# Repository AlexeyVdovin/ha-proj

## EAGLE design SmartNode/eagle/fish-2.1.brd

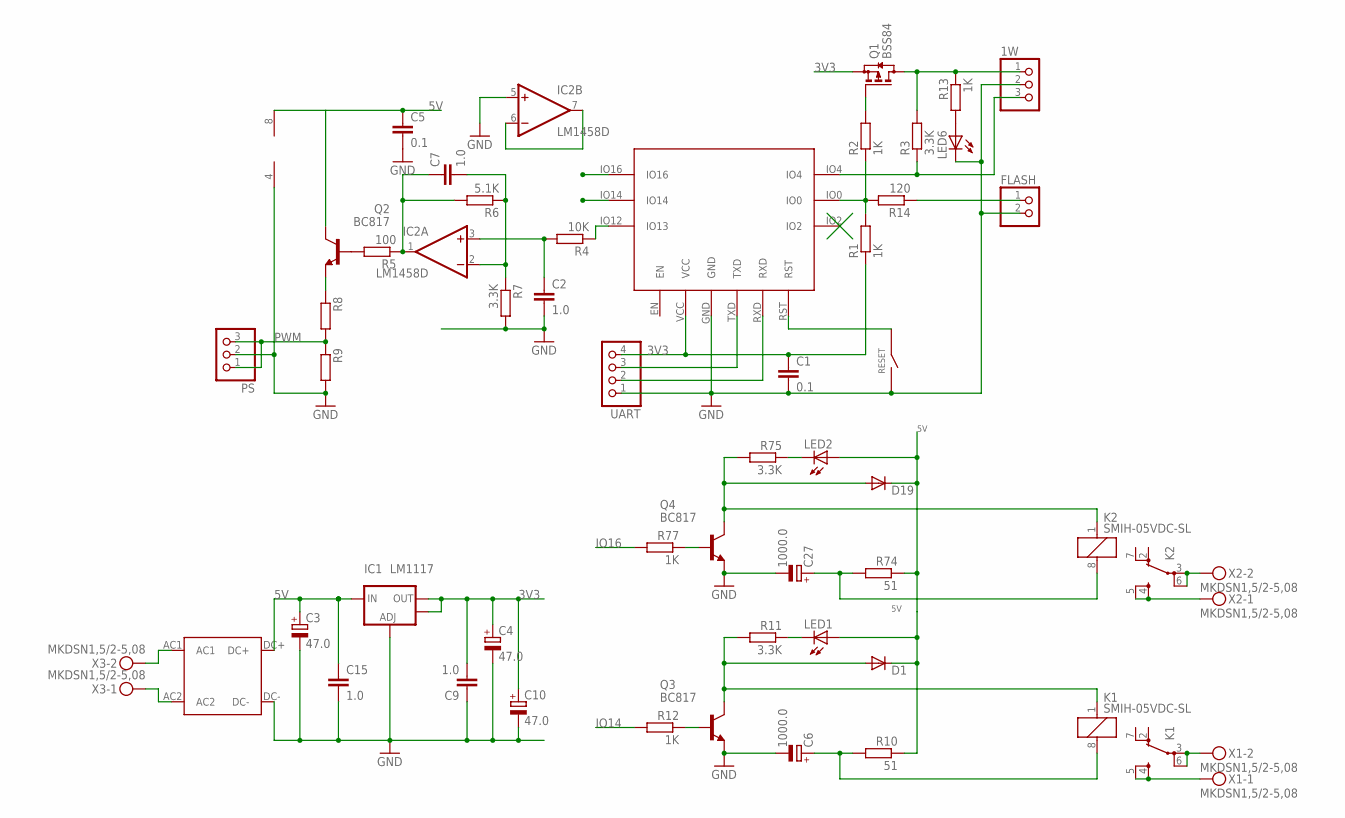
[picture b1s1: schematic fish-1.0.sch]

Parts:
1W: PINHD-1X3/90; 1X03/90
C1, C5: 0.1; C0805
C2, C7, C9, C15: 1.0; C0805
C3, C10: 47.0; SMC_D
C4: 47.0; SMC_B
C6, C27: 1000.0; E3,5-8
D1, D19: DIODE-SOD123; SOD123
ESP-M3: ESP-M3
FLASH: PINHD-1X2/90; 1X02/90
IC1: LM1117; SOT223
IC2: LM1458D; SO08
K1, K2: SMIH-05VDC-SL; FTR-K1C
LED1, LED2, LED6: LEDSMT1206; 1206
PS: PINHD-1X3/90; 1X03/90
Q1: BSS84; SOT23
Q2, Q3, Q4: BC817; SOT23-BEC
R1, R2, R12, R13, R77: 1K; R0603
R3, R7, R11, R75: 3.3K; R0603
R4: 10K; R0603
R5: 100; R0603
R6: 5.1K; R0603
R8, R9: R-EU_R0603; R0603
R10, R74: 51; R1206
R14: 120; R0603
RESET: TACT3X4
U$1: AC-DC/10W-12V; AC-DC/10W
UART: PINHD-1X4/90; 1X04/90
X1, X2, X3: MKDSN1,5/2-5,08

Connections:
1W: 1W.3, ESP-M3.IO4, R3.1
3V3: C1.1, C4.+, C9.2, C10.+, ESP-M3.VCC, IC1.2 (OUT), IC1.4 (OUT), Q1.2 (S), R1.1, UART.4; also elsewhere on the board
5V: C3.+, C5.1, C15.1, D1.C, D19.C, IC1.3 (IN), IC2.8 (V+), LED1.A, LED2.A, Q2.C, R10.1, R74.1, U$1.DC+; also elsewhere on the board
FLASH: FLASH.1, R14.1
GND: 1W.2, C1.2, C2.2, C3.-, C4.-, C5.2, C6.-, C9.1, C10.-, C15.2, C27.-, ESP-M3.GND, FLASH.2, IC1.1 (ADJ), IC2.4 (V-), IC2.5 (+IN), LED6.C, PS.2, Q3.E, Q4.E, R7.2, R9.2, RESET.P$2, U$1.DC-, UART.1; also elsewhere on the board
IO14: ESP-M3.IO14, R12.2
IO16: ESP-M3.IO16, R77.2
unnamed: Q1.1 (G), R2.2
unnamed 10: U$1.AC1, X3.2; also elsewhere on the board
unnamed: ESP-M3.IO12 (IO13), R4.1
unnamed 12: U$1.AC2, X3.1; also elsewhere on the board
unnamed: C2.1, IC2.3 (+IN), R4.2
unnamed 14: C7.1, IC2.1 (OUT), R5.1, R6.2; also elsewhere on the board
unnamed: C7.2, IC2.2 (-IN), R6.1, R7.1
unnamed 16: D1.A, K1.1, Q3.C, R11.2; also elsewhere on the board
unnamed: Q2.B, R5.2
unnamed: Q2.E, R8.1
unnamed: C6.+, K1.8 (2), R10.2
unnamed: LED1.C, R11.1
unnamed 21: Q3.B, R12.1; also elsewhere on the board
unnamed: K1.3 (PA), K1.6 (PB), X1.2
unnamed: ESP-M3.IO0, R1.2, R2.1, R14.2
unnamed: LED6.A, R13.2
unnamed: IC2.6 (-IN), IC2.7 (OUT)
unnamed: K1.4 (SA), K1.5 (SB), X1.1
unnamed 27: D19.A, K2.1, Q4.C, R75.2; also elsewhere on the board
unnamed: C27.+, K2.8 (2), R74.2
unnamed: LED2.C, R75.1
unnamed 30: Q4.B, R77.1; also elsewhere on the board
unnamed: K2.3 (PA), K2.6 (PB), X2.2
unnamed: K2.4 (SA), K2.5 (SB), X2.1
PWM: PS.1, PS.3, R8.2, R9.1; also elsewhere on the board
RST: ESP-M3.RST, RESET.P$1
RX1: ESP-M3.RXD, UART.2
TX1: ESP-M3.TXD, UART.3
VCC: 1W.1, Q1.3 (D), R3.2, R13.1

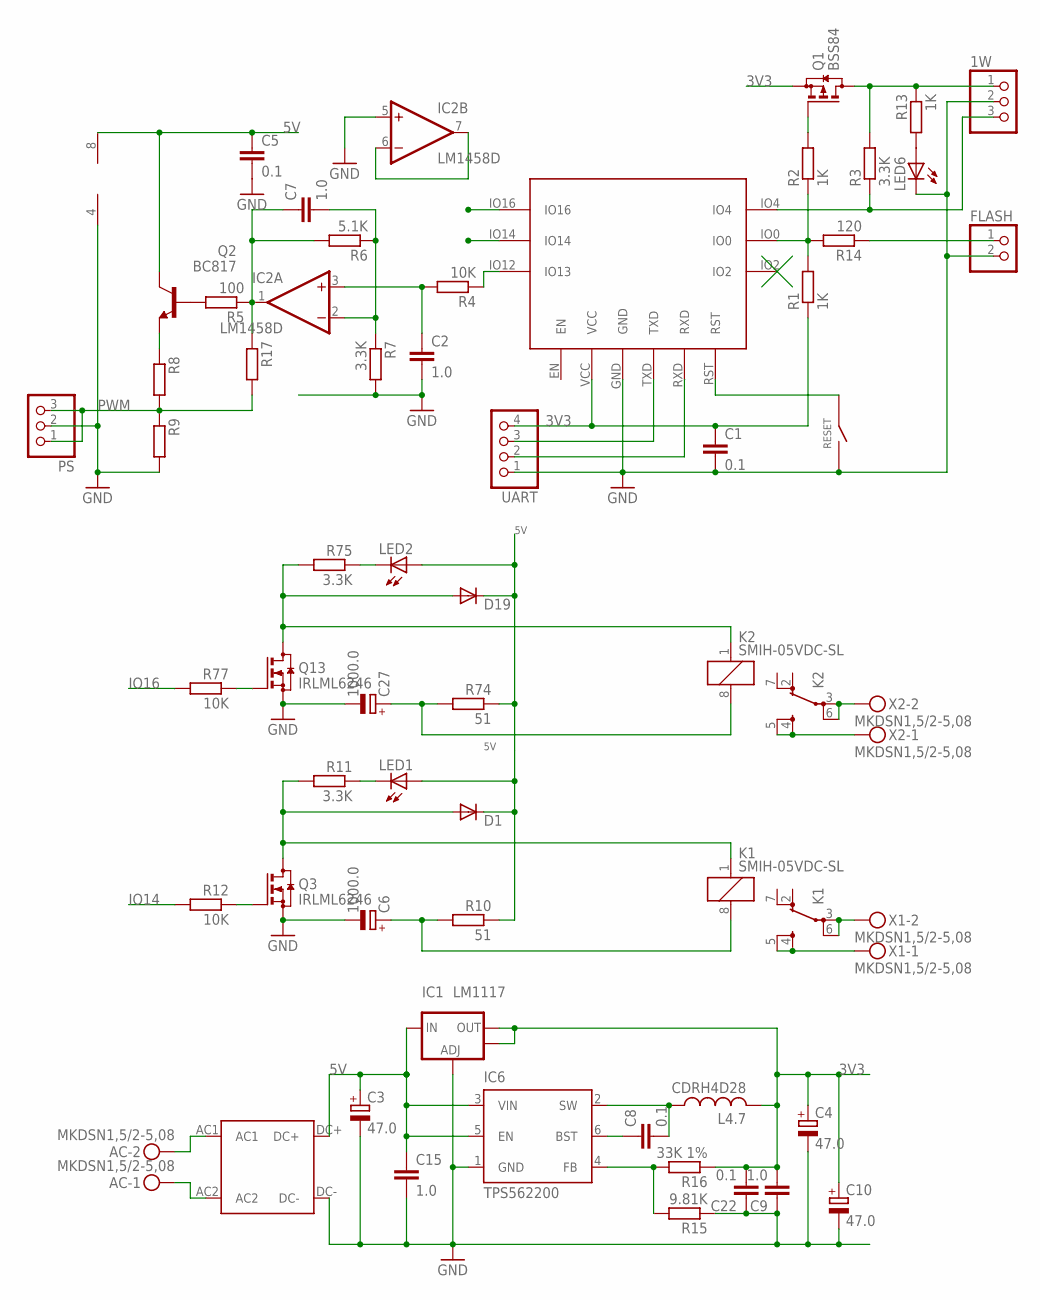
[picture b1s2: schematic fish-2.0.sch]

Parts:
1W: PINHD-1X3/90; 1X03/90
AC: MKDSN1,5/2-5,08
C1, C5, C8, C22: 0.1; C0805
C2, C7, C9, C15: 1.0; C0805
C3, C10: 47.0; SMC_D
C4: 47.0; SMC_B
C6, C27: 1000.0; E3,5-8
D1, D19: DIODE-SOD123; SOD123
ESP-M3: ESP-M3
FLASH: PINHD-1X2/90; 1X02/90
IC1: LM1117; SOT223
IC2: LM1458D; SO08
IC6: TPS562200; TSOT23-6_DDC
K1, K2: SMIH-05VDC-SL; FTR-K1C
L4.7: CDRH4D28
LED1, LED2, LED6: LEDSMT1206; 1206
PS: PINHD-1X3/90; 1X03/90
Q1: BSS84; SOT23
Q2: BC817; SOT23-BEC
Q3, Q13: IRLML6246; SOT23
R1, R2, R13: 1K; R0603
R3, R7, R11, R75: 3.3K; R0603
R4, R12, R77: 10K; R0603
R5: 100; R0603
R6: 5.1K; R0603
R8, R9, R17: R-EU_R0603; R0603
R10, R74: 51; R1206
R14: 120; R0603
R15: 9.81K; R0603
R16: 33K 1%; R0603
RESET: TACT3X4
U$1: AC-DC/10W-12V; AC-DC/10W
UART: PINHD-1X4/90; 1X04/90
X1, X2: MKDSN1,5/2-5,08

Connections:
1W: 1W.3, ESP-M3.IO4, R3.1
3V3: C1.1, C4.+, C9.2, C10.+, C22.2, ESP-M3.VCC, IC1.2 (OUT), IC1.4 (OUT), L4.7.P$2 (2), Q1.2 (S), R1.1, R16.1, UART.4
5V: C3.+, C5.1, C15.1, D1.C, D19.C, IC1.3 (IN), IC2.8 (V+), IC6.3 (VIN), IC6.5 (EN), LED1.A, LED2.A, Q2.C, R10.1, R74.1, U$1.DC+
BOOT: C8.1, IC6.6 (BST)
FB: IC6.4 (FB), R15.2, R16.2
FLASH: FLASH.1, R14.1
GND: 1W.2, C1.2, C2.2, C3.-, C4.-, C5.2, C6.-, C9.1, C10.-, C15.2, C22.1, C27.-, ESP-M3.GND, FLASH.2, IC1.1 (ADJ), IC2.4 (V-), IC2.5 (+IN), IC6.1 (GND), LED6.C, PS.2, Q3.2 (S), Q13.2 (S), R7.2, R9.2, R15.1, RESET.P$2, U$1.DC-, UART.1; also elsewhere on the board
IO14: ESP-M3.IO14, R12.2
IO16: ESP-M3.IO16, R77.2
unnamed: Q1.1 (G), R2.2
unnamed 10: AC.2, U$1.AC1; also elsewhere on the board
unnamed: ESP-M3.IO12 (IO13), R4.1
unnamed 12: AC.1, U$1.AC2; also elsewhere on the board
unnamed: C2.1, IC2.3 (+IN), R4.2
unnamed: C7.1, IC2.1 (OUT), R5.1, R6.2, R17.1
unnamed: C7.2, IC2.2 (-IN), R6.1, R7.1
unnamed 16: D1.A, K1.1, Q3.3 (D), R11.2; also elsewhere on the board
unnamed: Q2.B, R5.2
unnamed: Q2.E, R8.1
unnamed: C6.+, K1.8 (2), R10.2
unnamed: LED1.C, R11.1
unnamed 21: Q3.1 (G), R12.1; also elsewhere on the board
unnamed: K1.3 (PA), K1.6 (PB), X1.2
unnamed: ESP-M3.IO0, R1.2, R2.1, R14.2
unnamed: LED6.A, R13.2
unnamed: IC2.6 (-IN), IC2.7 (OUT)
unnamed: K1.4 (SA), K1.5 (SB), X1.1
unnamed 27: D19.A, K2.1, Q13.3 (D), R75.2; also elsewhere on the board
unnamed: C27.+, K2.8 (2), R74.2
unnamed: LED2.C, R75.1
unnamed 30: Q13.1 (G), R77.1; also elsewhere on the board
unnamed: K2.3 (PA), K2.6 (PB), X2.2
unnamed: K2.4 (SA), K2.5 (SB), X2.1
PWM: PS.1, PS.3, R8.2, R9.1, R17.2
RST: ESP-M3.RST, RESET.P$1
RX1: ESP-M3.RXD, UART.2
SW: C8.2, IC6.2 (SW), L4.7.P$1 (1)
TX1: ESP-M3.TXD, UART.3
VCC: 1W.1, Q1.3 (D), R3.2, R13.1

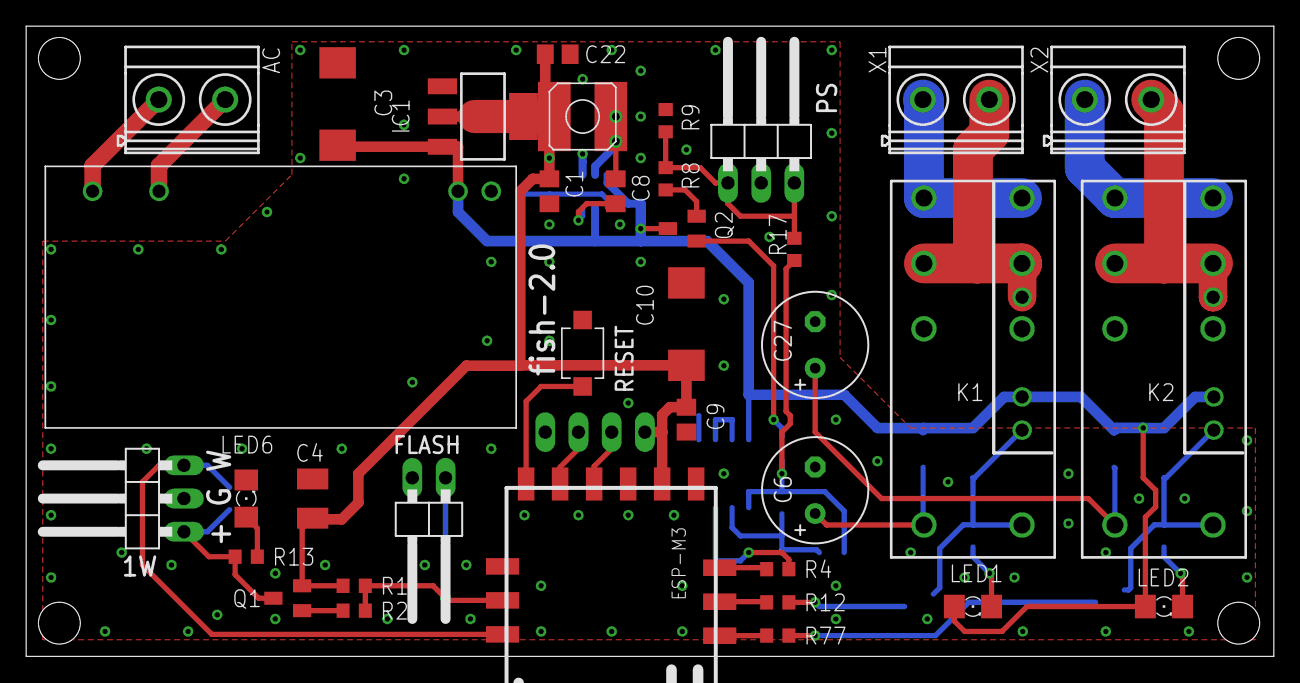
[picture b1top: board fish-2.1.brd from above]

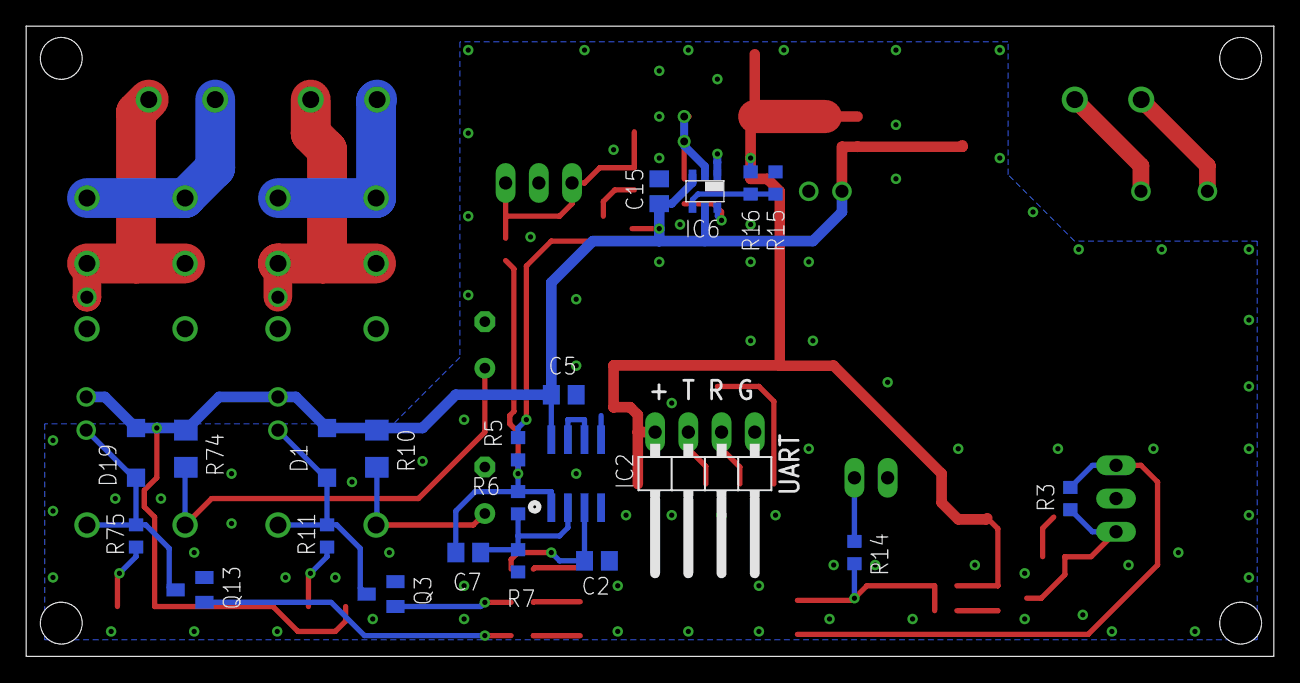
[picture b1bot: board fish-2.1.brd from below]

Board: 2 copper layers, 95.4 x 48.2 mm, 58 parts (22 on the bottom side), 39 nets.

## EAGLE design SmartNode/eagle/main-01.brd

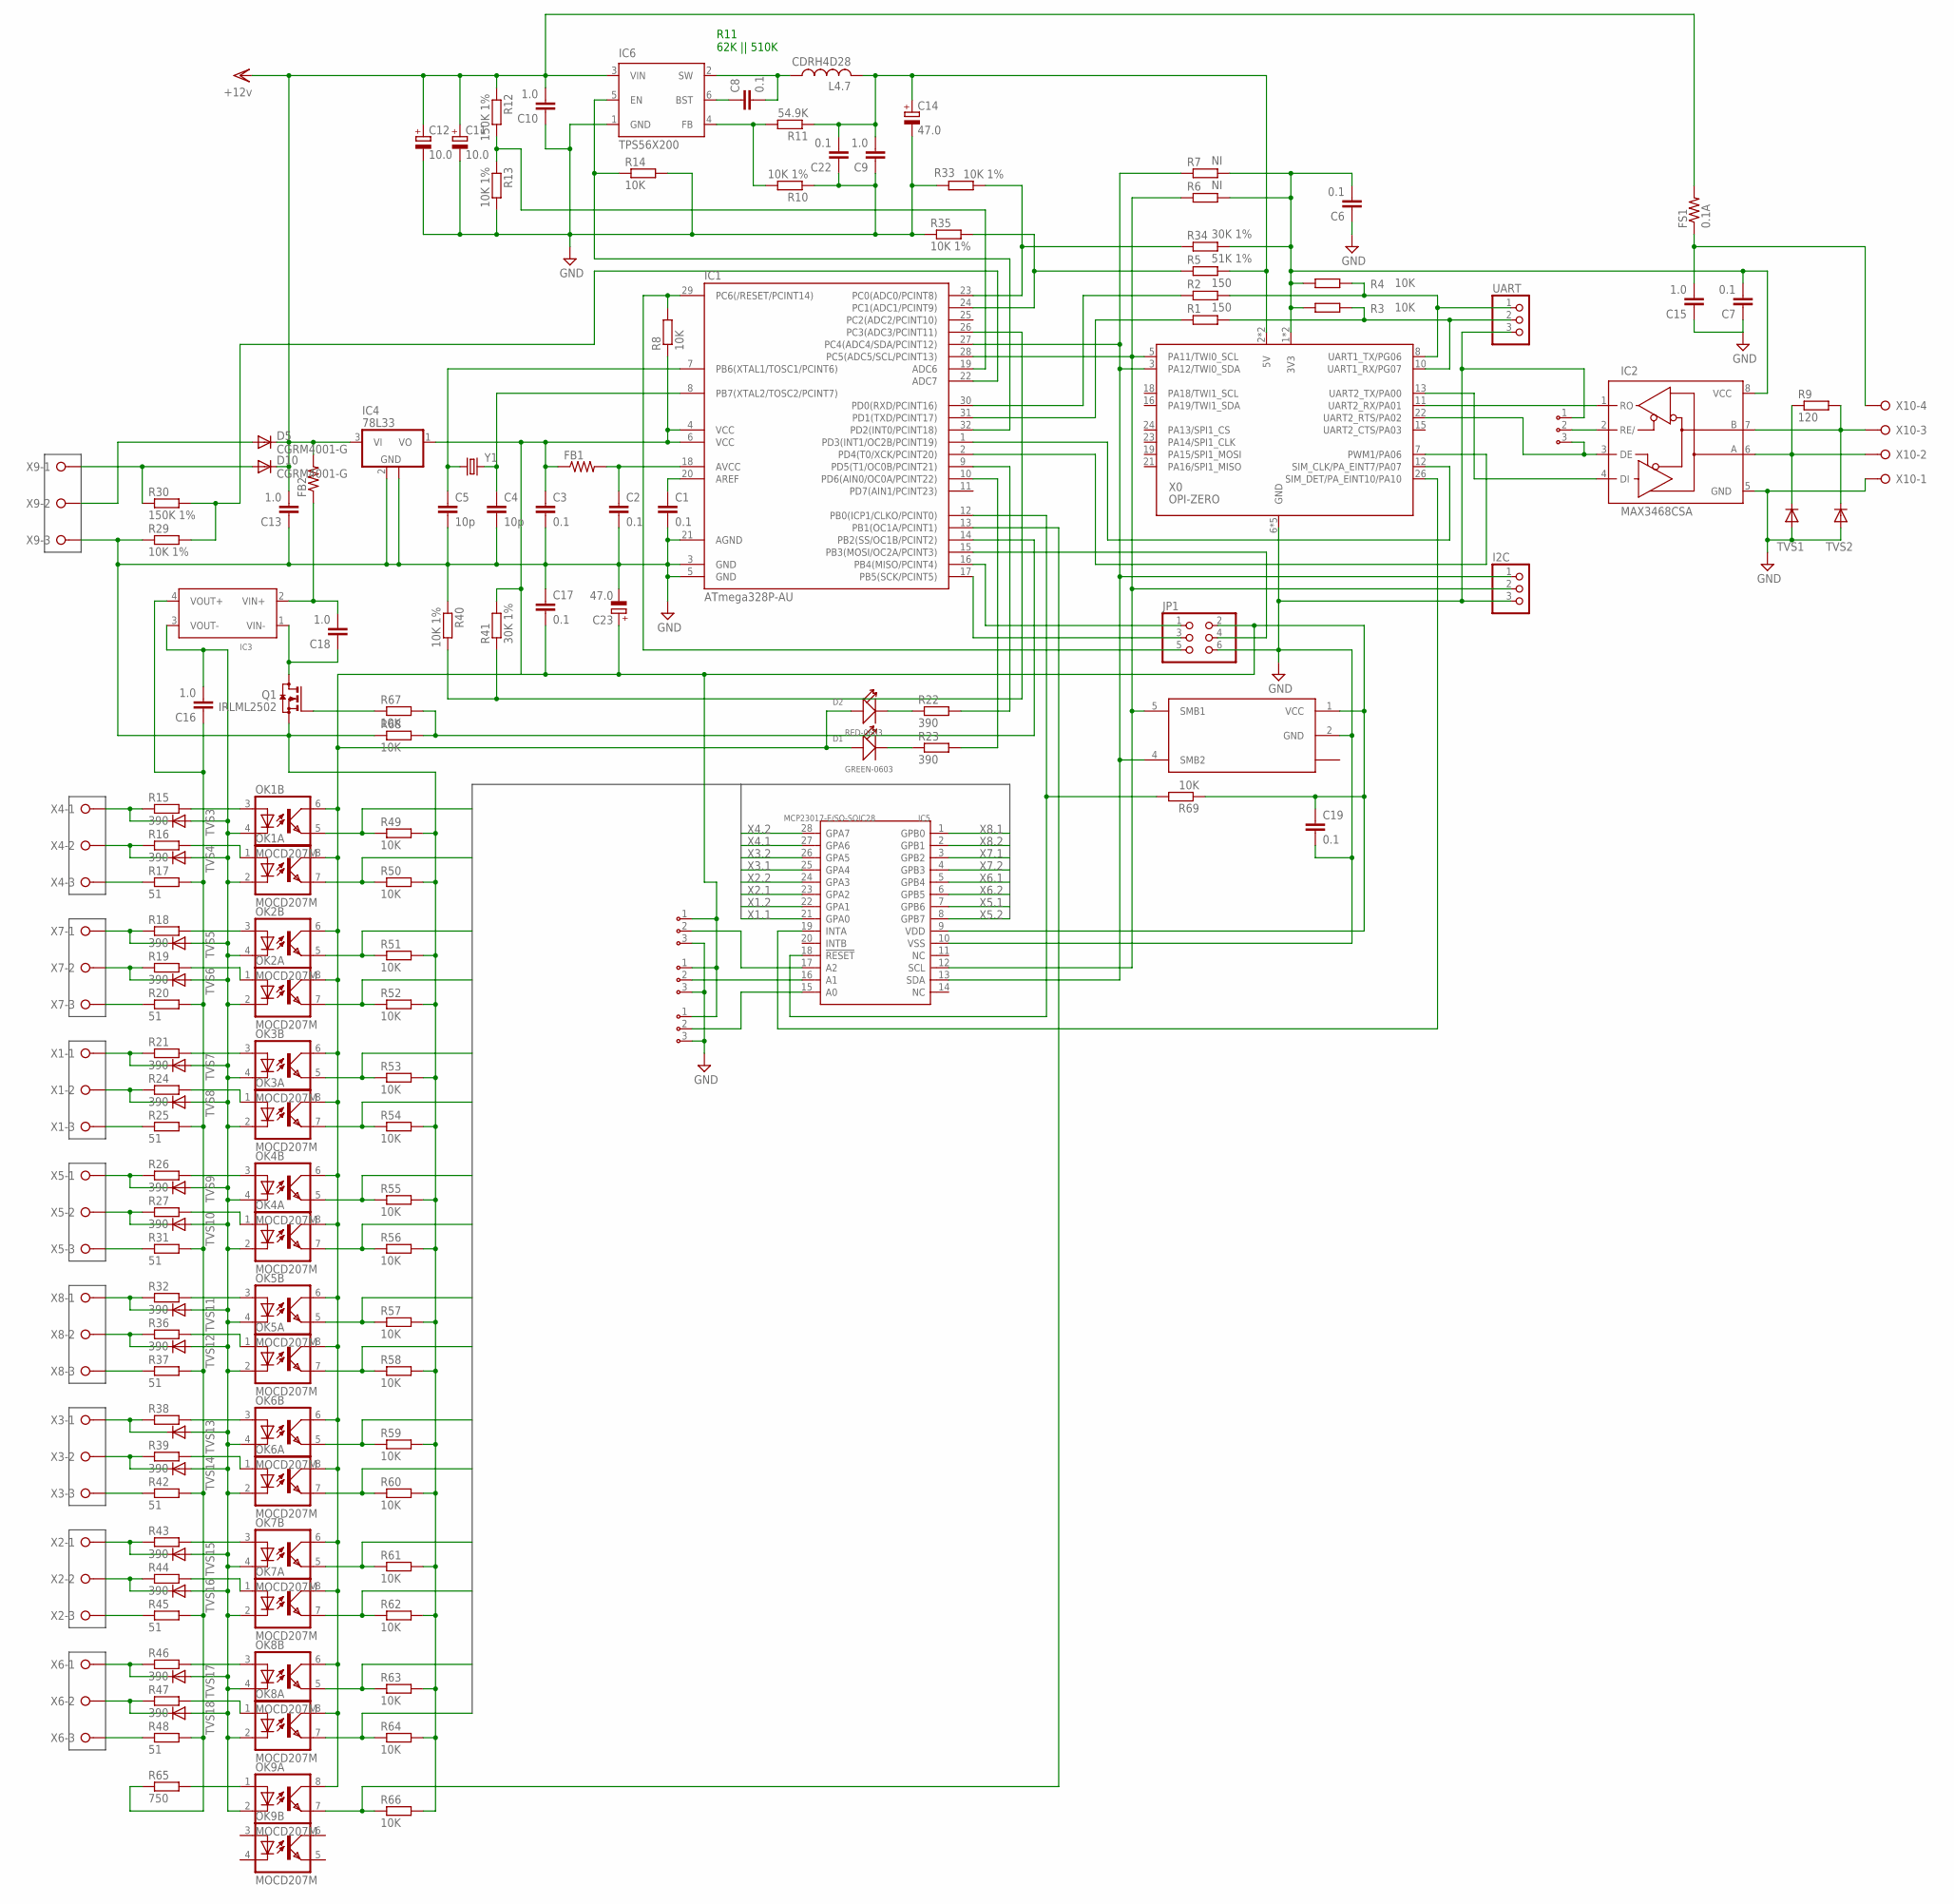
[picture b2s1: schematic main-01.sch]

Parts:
4: ADDR3PIN0603; 0603-3PIN
A0, A1, A2: ADDR3PIN0603; 0603-3PIN
C1, C2, C3, C17, C19: 0.1; C0603
C4, C5: 10p; C0603
C6, C7, C8, C22: 0.1; C0805
C9: 1.0; C0805
C10, C13, C15, C16, C18: 1.0; C1206
C11, C12: 10.0; C/6032-28R
C14, C23: 47.0; B/3528-21R
D1: GREEN-0603; LED-0603
D2: RED-0603; LED-0603
D5, D10: CGRM4001-G; SOD-123_MINI-SMA
FB1: R-US_R0805; R0805
FB2: R-US_R1206; R1206
FS1: 0.1A; R1210
I2C: PINHD-1X3; 1X03
IC1: ATmega328P-AU; TQFP32-08
IC2: MAX3468CSA; SO08
IC3: DC-DC-CONV-4PIN-ISOLATINGMURATA-NME-05-12-SERIES; DC-DC-MURATA-NME-05-12-SERIES
IC4: 78L33; SOT89
IC5: MCP23017-E/SO-SOIC28; SOIC28-1.27-17.9X7.5MM
IC6: TPS56X200; TSOT23-6_DDC
IC7: LTC1694; SOT23-5
JP1: PINHD-2X3; 2X03
L4.7: CDRH4D28
OK1, OK2, OK3, OK4, OK5, OK6, OK7, OK8, OK9: MOCD207M; SOIC08-FAIRCHILD
Q1: IRLML2502; SOT23
R1, R2: 150; R0603
R3, R4, R8, R14, R49, R50, R51, R52, R53, R54, R55, R56, R57, R58, R59, R60, R61, R62, R63, R64, R66, R67, R68, R69: 10K; R0603
R5: 51K 1%; R0603
R6, R7: NI; R0603
R9: 120; R1206
R10, R13, R29, R33, R35, R40: 10K 1%; R0603
R11: 54.9K; R0603
R12, R30: 150K 1%; R0603
R15, R16, R18, R19, R21, R22, R23, R24, R26, R27, R32, R36, R39, R43, R44, R46, R47: 390; R0603
R17, R20, R25, R31, R37, R42, R45, R48: 51; R0603
R34, R41: 30K 1%; R0603
R38: R-EU_R0603; R0603
R65: 750; R0603
TVS1, TVS2, TVS3, TVS4, TVS5, TVS6, TVS7, TVS8, TVS9, TVS10, TVS11, TVS12, TVS13, TVS14, TVS15, TVS16, TVS17, TVS18: DIODE-SOD323-W; SOD323-W
UART: PINHD-1X3; 1X03
X0: OPI-ZERO; OPI0
X1, X2, X3, X4, X5, X6, X7, X8, X9: W237-03P; W237-133
X10: W237-04P; W237-4P
Y1: CRYSTALHC49US; HC49US

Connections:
12V: C10.2, C11.+, C12.+, C13.2, D5.C, D10.C, FB2.2, FS1.2, IC4.3 (VI), IC6.3 (VIN), R12.1
GND: 4.1, A0.3, A1.3, A2.3, C1.2, C2.2, C3.2, C4.2, C5.2, C6.1, C7.1, C9.1, C10.1, C11.-, C12.-, C13.1, C14.-, C15.1, C17.1, C19.2, C22.1, C23.-, I2C.3, IC1.3 (GND), IC1.5 (GND), IC1.21 (AGND), IC2.5 (GND), IC4.2 (GND), IC4.2@1 (GND), IC5.10 (VSS), IC6.1 (GND), IC7.2 (GND), JP1.6, Q1.2 (S), R10.1, R13.2, R14.2, R29.1, R33.2, R35.1, R40.1, R49.2, R50.2, R51.2, R52.2, R53.2, R54.2, R55.2, R56.2, R57.2, R58.2, R59.2, R60.2, R61.2, R62.2, R63.2, R64.2, R66.2, R68.1, TVS1.A, TVS2.A, UART.3, X0.6 (GND), X0.9 (GND), X0.14 (GND), X0.20 (GND), X0.25 (GND), X9.3, X10.1
unnamed: 4.3, IC2.3 (DE), X0.22 (UART2_RTS/PA02)
unnamed: IC2.1 (RO), X0.11 (UART2_RX/PA01)
unnamed: C8.2, IC6.2 (SW), L4.7.P$1 (1)
unnamed: C4.1, IC1.8 (PB7(XTAL2/TOSC2/PCINT7)), Y1.2
unnamed: IC1.30 (PD0(RXD/PCINT16)), R2.1
unnamed: IC1.31 (PD1(TXD/PCINT17)), R1.1
unnamed: R1.2, R3.2, UART.2, X0.10 (UART1_RX/PG07)
unnamed: R2.2, R4.2, UART.1, X0.8 (UART1_TX/PG06)
unnamed: IC2.4 (DI), X0.13 (UART2_TX/PA00)
unnamed: C5.1, IC1.7 (PB6(XTAL1/TOSC1/PCINT6)), Y1.1
unnamed: IC1.24 (PC1(ADC1/PCINT9)), R5.1, R35.2
unnamed: D5.A, X9.2
unnamed: IC1.29 (PC6(/RESET/PCINT14)), JP1.5, R8.2
unnamed: OK1.3 (A), R15.2
unnamed: C1.1, IC1.20 (AREF)
unnamed: C2.1, FB1.2, IC1.18 (AVCC)
unnamed: C8.1, IC6.6 (BST)
unnamed: IC1.15 (PB3(MOSI/OC2A/PCINT3)), JP1.4
unnamed: IC1.17 (PB5(SCK/PCINT5)), JP1.3
unnamed: IC1.16 (PB4(MISO/PCINT4)), JP1.1
unnamed: IC2.6 (A), R9.1, TVS1.C, X10.2
unnamed: IC6.4 (FB), R10.2, R11.2
unnamed: IC2.7 (B), R9.2, TVS2.C, X10.3
unnamed: C15.2, FS1.1, X10.4
unnamed: IC1.19 (ADC6), R12.2, R13.1
unnamed: R15.1, TVS3.C, X4.1
unnamed: IC1.32 (PD2(INT0/PCINT18)), IC6.5 (EN), R14.1
unnamed: R16.1, TVS4.C, X4.2
unnamed: IC1.1 (PD3(INT1/OC2B/PCINT19)), X0.12 (SIM_CLK/PA_EINT7/PA07)
unnamed: R17.1, X4.3
unnamed: D10.A, R30.1, X9.1
unnamed: R18.1, TVS5.C, X7.1
unnamed: R19.1, TVS6.C, X7.2
unnamed: R20.1, X7.3
unnamed: OK2.3 (A), R18.2
unnamed: R21.1, TVS7.C, X1.1
unnamed: IC1.10 (PD6(AIN0/OC0A/PCINT22)), R23.2
unnamed: IC1.9 (PD5(T1/OC0B/PCINT21)), R22.2
unnamed: OK3.3 (A), R21.2
unnamed: R24.1, TVS8.C, X1.2
unnamed: R25.1, X1.3
unnamed: R26.1, TVS9.C, X5.1
unnamed: R27.1, TVS10.C, X5.2
unnamed: R31.1, X5.3
unnamed: R32.1, TVS11.C, X8.1
unnamed: R36.1, TVS12.C, X8.2
unnamed: R37.1, X8.3
unnamed: R38.1, TVS13.C, X3.1
unnamed: R39.1, TVS14.C, X3.2
unnamed: R42.1, X3.3
unnamed: R43.1, TVS15.C, X2.1
unnamed: R44.1, TVS16.C, X2.2
unnamed: R45.1, X2.3
unnamed: R46.1, TVS17.C, X6.1
unnamed: R47.1, TVS18.C, X6.2
unnamed: R48.1, X6.3
unnamed: OK4.3 (A), R26.2
unnamed: OK5.3 (A), R32.2
unnamed: OK6.3 (A), R38.2
unnamed: OK7.3 (A), R43.2
unnamed: IC1.22 (ADC7), R29.2, R30.2
unnamed: OK8.3 (A), R46.2
unnamed: C16.1, IC3.4 (VOUT+), R17.2, R20.2, R25.2, R31.2, R37.2, R42.2, R45.2, R48.2, R65.1
unnamed: IC1.23 (PC0(ADC0/PCINT8)), R33.1, R34.1
unnamed: OK1.1 (A), R16.2
unnamed: OK2.1 (A), R19.2
unnamed: OK3.1 (A), R24.2
unnamed: IC1.26 (PC3(ADC3/PCINT11)), R40.2, R41.1
unnamed: OK4.1 (A), R27.2
unnamed: OK5.1 (A), R36.2
unnamed: OK6.1 (A), R39.2
unnamed: OK7.1 (A), R44.2
unnamed: OK8.1 (A), R47.2
unnamed: C16.2, IC3.3 (VOUT-), OK1.2 (C), OK1.4 (C), OK2.2 (C), OK2.4 (C), OK3.2 (C), OK3.4 (C), OK4.2 (C), OK4.4 (C), OK5.2 (C), OK5.4 (C), OK6.2 (C), OK6.4 (C), OK7.2 (C), OK7.4 (C), OK8.2 (C), OK8.4 (C), OK9.2 (C), TVS3.A, TVS4.A, TVS5.A, TVS6.A, TVS7.A, TVS8.A, TVS9.A, TVS10.A, TVS11.A, TVS12.A, TVS13.A, TVS14.A, TVS15.A, TVS16.A, TVS17.A, TVS18.A
unnamed: D2.-, R22.1
unnamed: 4.2, IC2.2 (RE/)
unnamed: IC1.2 (PD4(T0/XCK/PCINT20)), X0.7 (PWM1/PA06)
unnamed: IC5.19 (INTA), X0.26 (SIM_DET/PA_EINT10/PA10)
unnamed: OK9.1 (A), R65.2
unnamed: IC1.13 (PB1(OC1A/PCINT1)), OK9.7 (EMIT), R66.1
unnamed: Q1.1 (G), R67.1
unnamed: IC1.14 (PB2(SS/OC1B/PCINT2)), R67.2, R68.2
unnamed: C18.1, IC3.1 (VIN-), Q1.3 (D)
unnamed: C18.2, FB2.1, IC3.2 (VIN+)
unnamed: IC1.12 (PB0(ICP1/CLKO/PCINT0)), IC5.18 (!RESET), R69.2
unnamed: A0.2, IC5.15 (A0)
unnamed: A1.2, IC5.16 (A1)
unnamed: A2.2, IC5.17 (A2)
unnamed: D1.-, R23.1
SCL: I2C.2, IC1.28 (PC5(ADC5/SCL/PCINT13)), IC5.12 (SCL), IC7.5 (SMB1), R6.1, X0.5 (PA11/TWI0_SCL)
SDA: I2C.1, IC1.27 (PC4(ADC4/SDA/PCINT12)), IC5.13 (SDA), IC7.4 (SMB2), R7.1, X0.3 (PA12/TWI0_SDA)
VCC: A0.1, A1.1, A2.1, C3.1, C17.2, C19.1, C23.+, D1.+, D2.+, FB1.1, IC1.4 (VCC), IC1.6 (VCC), IC4.1 (VO), IC5.9 (VDD), IC7.1 (VCC), JP1.2, OK1.6 (COL), OK1.8 (COL), OK2.6 (COL), OK2.8 (COL), OK3.6 (COL), OK3.8 (COL), OK4.6 (COL), OK4.8 (COL), OK5.6 (COL), OK5.8 (COL), OK6.6 (COL), OK6.8 (COL), OK7.6 (COL), OK7.8 (COL), OK8.6 (COL), OK8.8 (COL), OK9.8 (COL), R8.1, R41.2, R69.1
X1.1: IC5.21 (GPA0), OK3.5 (EMIT), R53.1
X1.2: IC5.22 (GPA1), OK3.7 (EMIT), R54.1
X2.1: IC5.23 (GPA2), OK7.5 (EMIT), R61.1
X2.2: IC5.24 (GPA3), OK7.7 (EMIT), R62.1
X3.1: IC5.25 (GPA4), OK6.5 (EMIT), R59.1
X3.2: IC5.26 (GPA5), OK6.7 (EMIT), R60.1
X4.1: IC5.27 (GPA6), OK1.5 (EMIT), R49.1
X4.2: IC5.28 (GPA7), OK1.7 (EMIT), R50.1
X5.1: IC5.7 (GPB6), OK4.5 (EMIT), R55.1
X5.2: IC5.8 (GPB7), OK4.7 (EMIT), R56.1
X6.1: IC5.5 (GPB4), OK8.5 (EMIT), R63.1
X6.2: IC5.6 (GPB5), OK8.7 (EMIT), R64.1
X7.1: IC5.3 (GPB2), OK2.5 (EMIT), R51.1
X7.2: IC5.4 (GPB3), OK2.7 (EMIT), R52.1
X8.1: IC5.1 (GPB0), OK5.5 (EMIT), R57.1
X8.2: IC5.2 (GPB1), OK5.7 (EMIT), R58.1
Z3V3: C6.2, C7.2, IC2.8 (VCC), R3.1, R4.1, R6.2, R7.2, R34.2, X0.1 (3V3), X0.17 (3V3)
Z5V: C9.2, C14.+, C22.2, L4.7.P$2 (2), R5.2, R11.1, X0.2 (5V), X0.4 (5V)

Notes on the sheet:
R11 62K || 510K

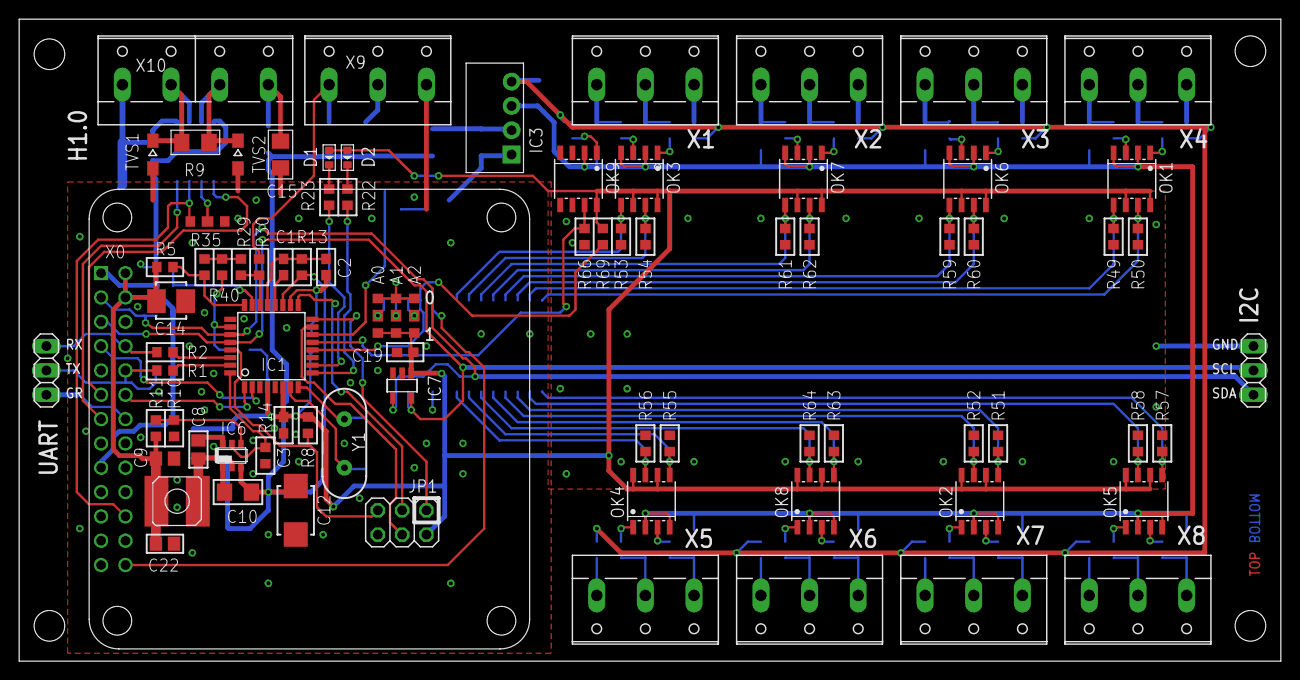
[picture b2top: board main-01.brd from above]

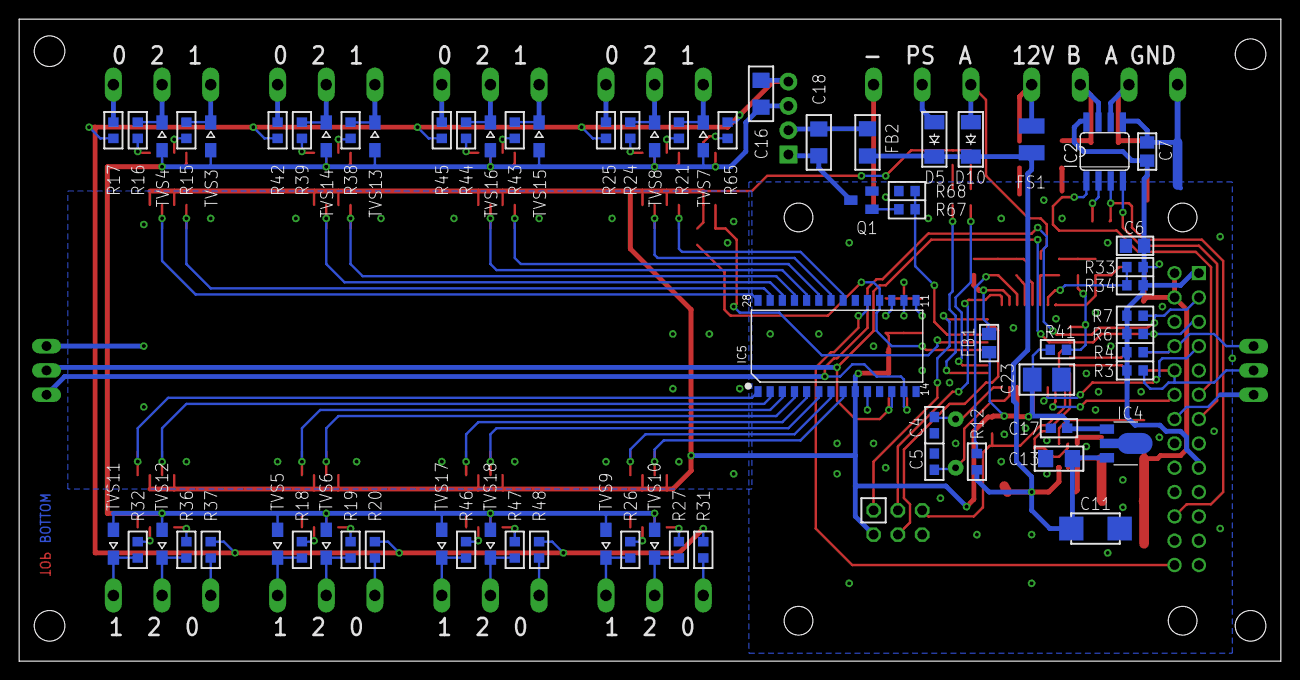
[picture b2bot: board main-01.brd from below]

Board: 2 copper layers, 131.8 x 67.0 mm, 151 parts (70 on the bottom side), 112 nets.

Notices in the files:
parts and their libraries:
SparkFun: Licensing: CC v3.0 Share-Alike You are welcome to use this library for commercial purposes.
